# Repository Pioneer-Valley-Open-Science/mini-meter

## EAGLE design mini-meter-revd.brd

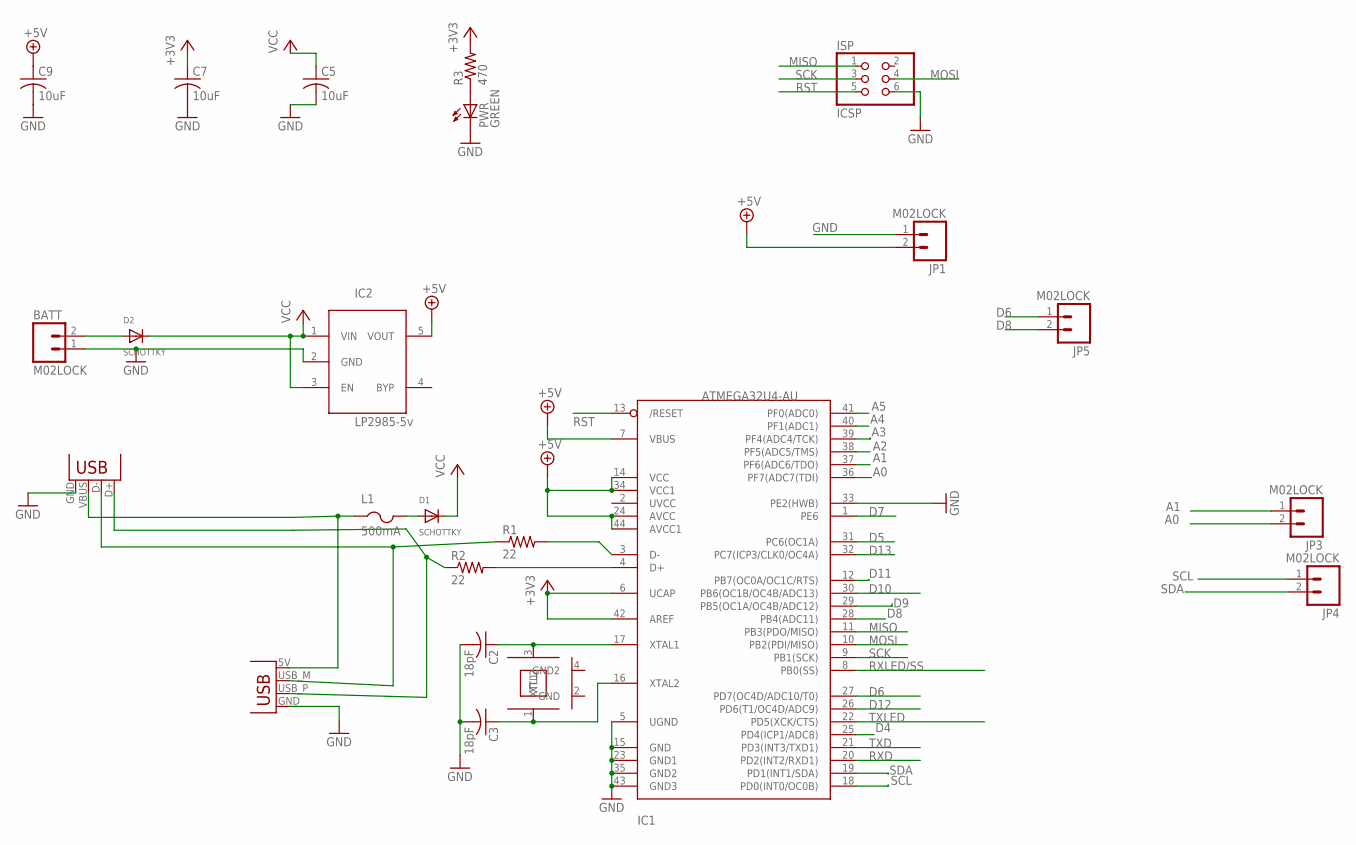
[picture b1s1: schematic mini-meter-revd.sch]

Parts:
BATT: M02LOCK; 1X02_LOCK
C2, C3: 18pF; C0805K
C5, C7, C9: 10uF; C0805K
D1, D2: SCHOTTKY; SOD-123
IC1: ATMEGA32U4-AU; TQFP44
IC2: LP2985-5v; SOT23-5L
ISP: ICSP; 2X03
JP1, JP3, JP4, JP5: M02LOCK; 1X02_LOCK
L1: 500mA; R1206
P1: USBPCB; USB-A-PCB
PWR: GREEN; CHIPLED_0805
R1, R2: 22; R0805
R3: 470; R0805
X1: USB-MICROB
XTL1: 16MHz; CRYSTAL-SMD-3X2

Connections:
+3V3: C7.1, IC1.6 (UCAP), IC1.42 (AREF), R3.2
+5V: C9.1, IC1.7 (VBUS), IC1.14 (VCC), IC1.24 (AVCC), IC1.34 (VCC1), IC1.44 (AVCC1), IC2.5 (VOUT), JP1.2
A0: IC1.36 (PF7(ADC7(TDI)), JP3.2
A1: IC1.37 (PF6(ADC6/TDO)), JP3.1
A2: IC1.38 (PF5(ADC5/TMS))
A3: IC1.39 (PF4(ADC4/TCK))
A4: IC1.40 (PF1(ADC1))
A5: IC1.41 (PF0(ADC0))
D4: IC1.25 (PD4(ICP1/ADC8))
D5: IC1.31 (PC6(OC1A))
D6: IC1.27 (PD7(OC4D/ADC10/T0)), JP5.1
D7: IC1.1 (PE6)
D8: IC1.28 (PB4(ADC11)), JP5.2
D9: IC1.29 (PB5(OC1A/OC4B/ADC12))
D10: IC1.30 (PB6(OC1B/OC4B/ADC13))
D11: IC1.12 (PB7(OC0A/OC1C/RTS))
D12: IC1.26 (PD6(T1/OC4D/ADC9))
D13: IC1.32 (PC7(ICP3/CLK0/OC4A))
GND: BATT.1, C2.2, C3.2, C5.2, C7.2, C9.2, IC1.5 (UGND), IC1.15 (GND), IC1.23 (GND1), IC1.33 (PE2(HWB)), IC1.35 (GND2), IC1.43 (GND3), IC2.2 (GND), ISP.6, JP1.1, P1.GND, PWR.C, X1.GND
MISO: IC1.11 (PB3(PDO/MISO)), ISP.1
MOSI: IC1.10 (PB2(PDI/MISO)), ISP.4
unnamed: PWR.A, R3.1
unnamed: P1.USB_P (D+), R2.1, X1.D+
unnamed: IC1.3 (D-), R1.2
unnamed: IC1.4 (D+), R2.2
unnamed: P1.USB_M (D-), R1.1, X1.D-
unnamed: BATT.2, D2.A
unnamed: C2.1, IC1.17 (XTAL1), XTL1.3 (XTL2)
unnamed: C3.1, IC1.16 (XTAL2), XTL1.1 (XTL1)
unnamed: D1.A, L1.2
RST: IC1.13 (/RESET), ISP.5
RXD: IC1.20 (PD2(INT2/RXD1))
RXLED/SS: IC1.8 (PB0(SS))
SCK: IC1.9 (PB1(SCK)), ISP.3
SCL: IC1.18 (PD0(INT0/OC0B)), JP4.1
SDA: IC1.19 (PD1(INT1/SDA)), JP4.2
TXD: IC1.21 (PD3(INT3/TXD1))
TXLED: IC1.22 (PD5(XCK/CTS))
VBUS: L1.1, P1.5V (VBUS), X1.VBUS
VCC: C5.1, D1.C, D2.C, IC2.1 (VIN), IC2.3 (EN)

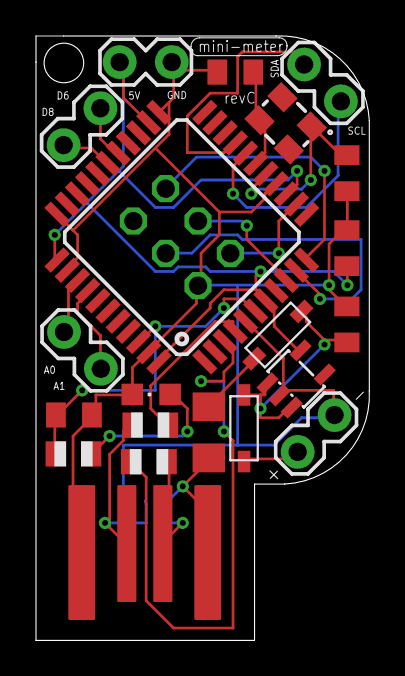
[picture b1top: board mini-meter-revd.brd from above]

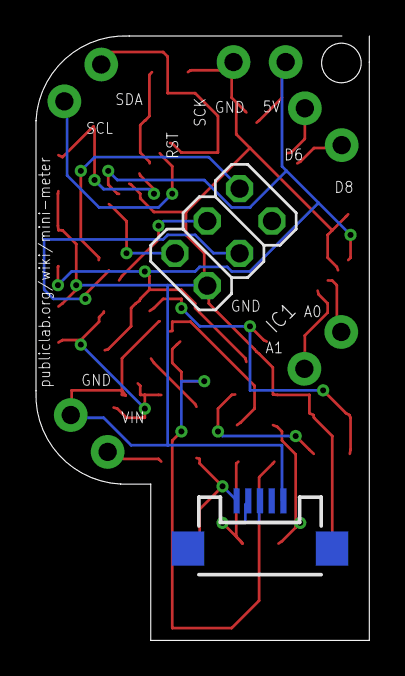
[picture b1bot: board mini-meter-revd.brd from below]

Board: 2 copper layers, 18.5 x 33.6 mm, 23 parts (2 on the bottom side), 24 nets.

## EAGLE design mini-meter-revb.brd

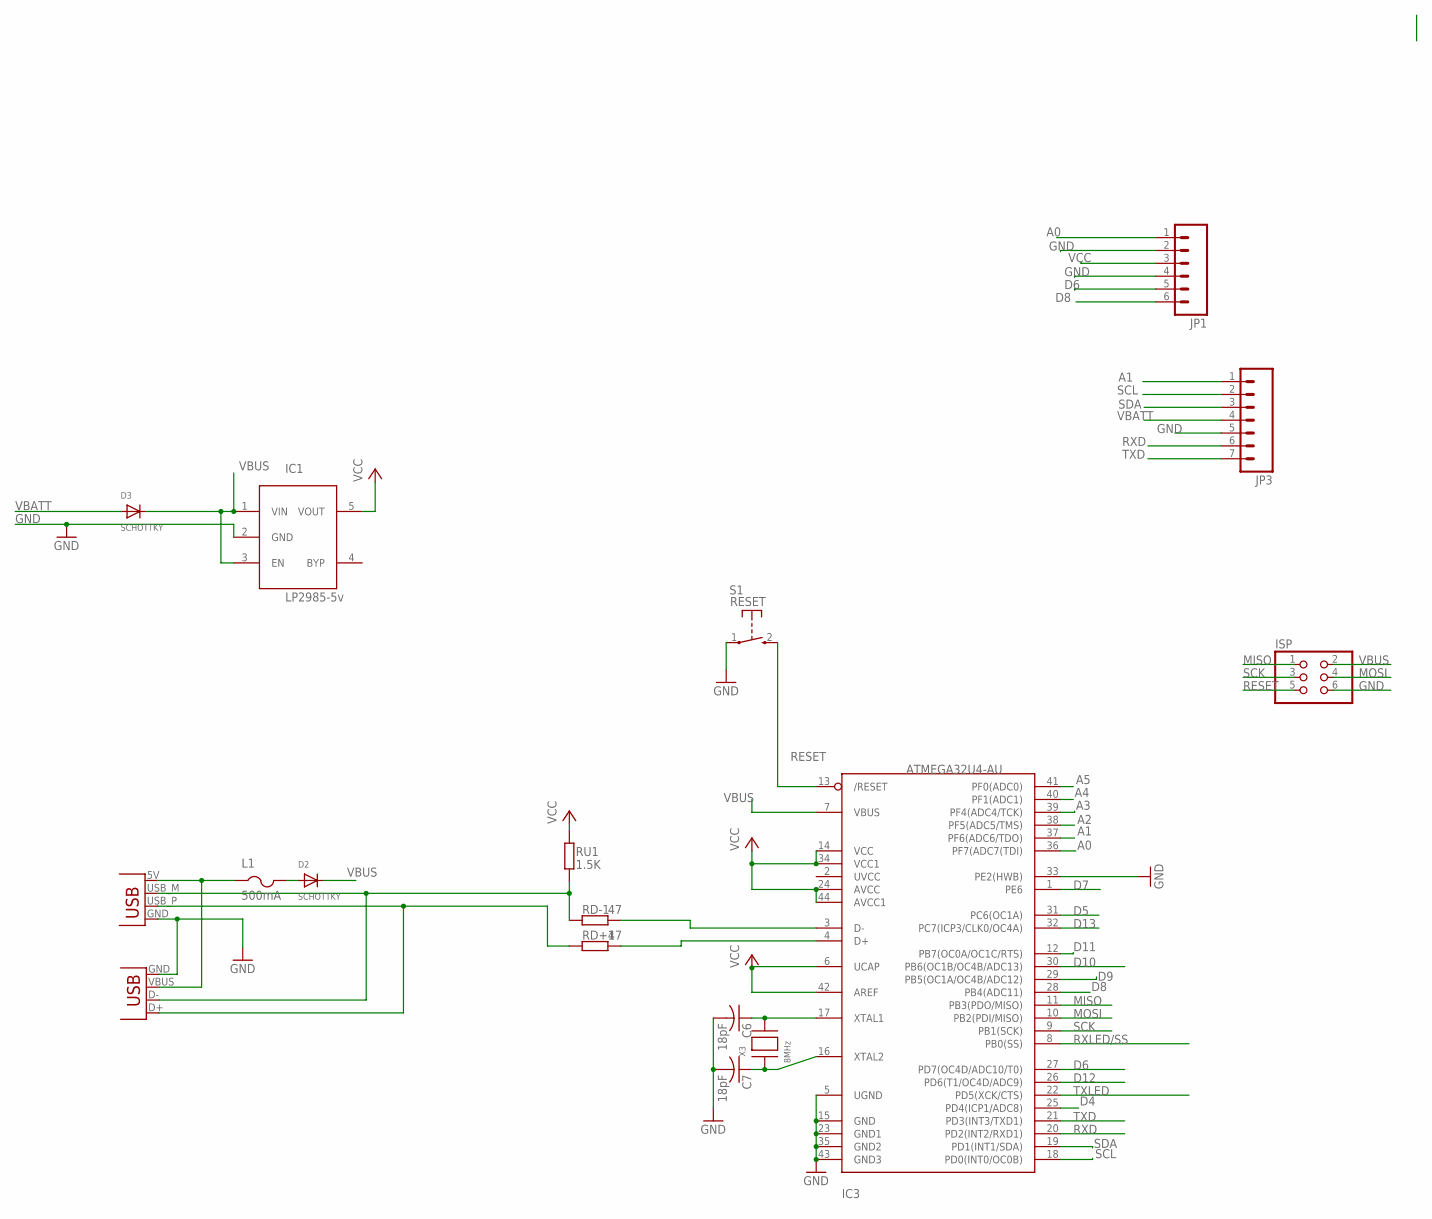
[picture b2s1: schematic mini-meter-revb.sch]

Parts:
C6, C7: 18pF; C0805K
D2, D3: SCHOTTKY; SOD-123
IC1: LP2985-5v; SOT23-5L
IC3: ATMEGA32U4-AU; TQFP44
ISP: PINHD-2X3; 2X03
JP1: M06LOCK; 1X06_LOCK
JP3: M07LOCK; 1X07_LOCK
L1: 500mA; R1206
P1: USBPCB; USB-A-PCB
RD+1: 47; R0805
RD-1: 47; R0805
RU1: 1.5K; R0805
S1: RESET; TACTILE_SWITCH_SMD_2PIN_TINY
X2: USBSMD; USB-MINIB
X3: 8MHz; NX5032

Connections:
A0: IC3.36 (PF7(ADC7(TDI)), JP1.1
A1: IC3.37 (PF6(ADC6/TDO)), JP3.1
A2: IC3.38 (PF5(ADC5/TMS))
A3: IC3.39 (PF4(ADC4/TCK))
A4: IC3.40 (PF1(ADC1))
A5: IC3.41 (PF0(ADC0))
D4: IC3.25 (PD4(ICP1/ADC8))
D5: IC3.31 (PC6(OC1A))
D6: IC3.27 (PD7(OC4D/ADC10/T0)), JP1.5
D7: IC3.1 (PE6)
D8: IC3.28 (PB4(ADC11)), JP1.6
D9: IC3.29 (PB5(OC1A/OC4B/ADC12))
D10: IC3.30 (PB6(OC1B/OC4B/ADC13))
D11: IC3.12 (PB7(OC0A/OC1C/RTS))
D12: IC3.26 (PD6(T1/OC4D/ADC9))
D13: IC3.32 (PC7(ICP3/CLK0/OC4A))
D-: P1.USB_M (D-), RD-1.1, RU1.1, X2.D-
GND: C6.2, C7.2, IC1.2 (GND), IC3.5 (UGND), IC3.15 (GND), IC3.23 (GND1), IC3.33 (PE2(HWB)), IC3.35 (GND2), IC3.43 (GND3), ISP.6, JP1.2, JP1.4, JP3.5, P1.GND, S1.1, X2.GND
MISO: IC3.11 (PB3(PDO/MISO)), ISP.1
MOSI: IC3.10 (PB2(PDI/MISO)), ISP.4
unnamed: D2.A, L1.2
unnamed: C7.1, IC3.16 (XTAL2), X3.P$1
unnamed: C6.1, IC3.17 (XTAL1), X3.P$2
unnamed: P1.USB_P (D+), RD+1.1, X2.D+
unnamed: IC3.4 (D+), RD+1.2
unnamed: IC3.3 (D-), RD-1.2
RESET: IC3.13 (/RESET), ISP.5, S1.2 (S)
RXD: IC3.20 (PD2(INT2/RXD1)), JP3.6
RXLED/SS: IC3.8 (PB0(SS))
SCK: IC3.9 (PB1(SCK)), ISP.3
SCL: IC3.18 (PD0(INT0/OC0B)), JP3.2
SDA: IC3.19 (PD1(INT1/SDA)), JP3.3
TXD: IC3.21 (PD3(INT3/TXD1)), JP3.7
TXLED: IC3.22 (PD5(XCK/CTS))
VBATT: D3.A, JP3.4
VBUS: D2.C, D3.C, IC1.1 (VIN), IC1.3 (EN), IC3.7 (VBUS), ISP.2
VBUS1: L1.1, P1.5V (VBUS), X2.VBUS
VCC: IC1.5 (VOUT), IC3.6 (UCAP), IC3.14 (VCC), IC3.24 (AVCC), IC3.34 (VCC1), IC3.42 (AREF), IC3.44 (AVCC1), JP1.3, RU1.2

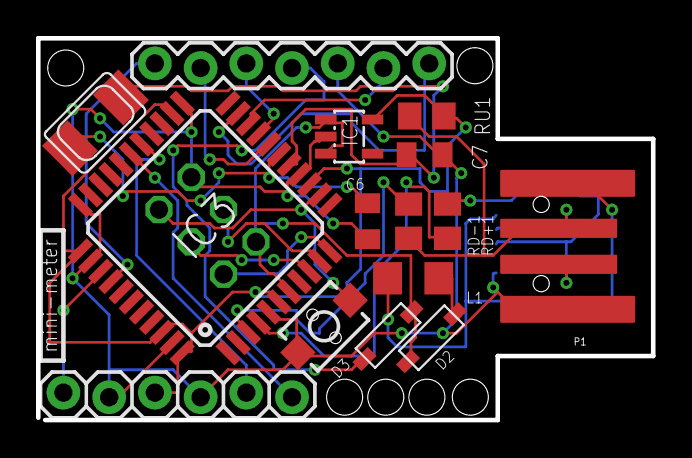
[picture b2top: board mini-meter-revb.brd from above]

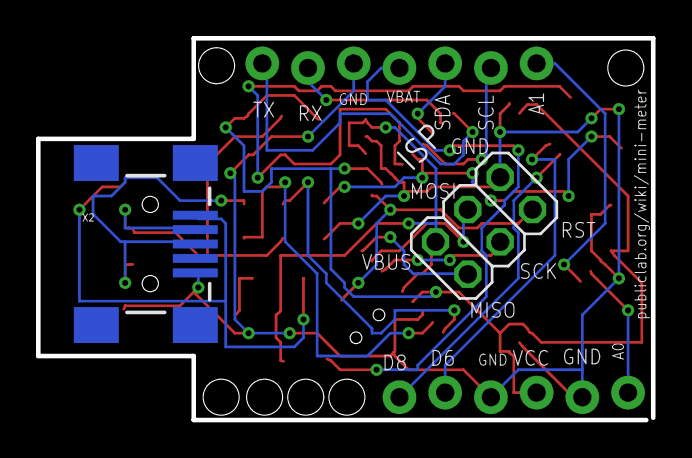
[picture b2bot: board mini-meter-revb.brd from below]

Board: 2 copper layers, 34.2 x 21.2 mm, 17 parts (2 on the bottom side), 24 nets.

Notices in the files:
parts and their libraries:
SparkFun-Connectors: Licensing: Creative Commons ShareAlike 4.0 International - https://creativecommons.org/licenses/by-sa/4.0
